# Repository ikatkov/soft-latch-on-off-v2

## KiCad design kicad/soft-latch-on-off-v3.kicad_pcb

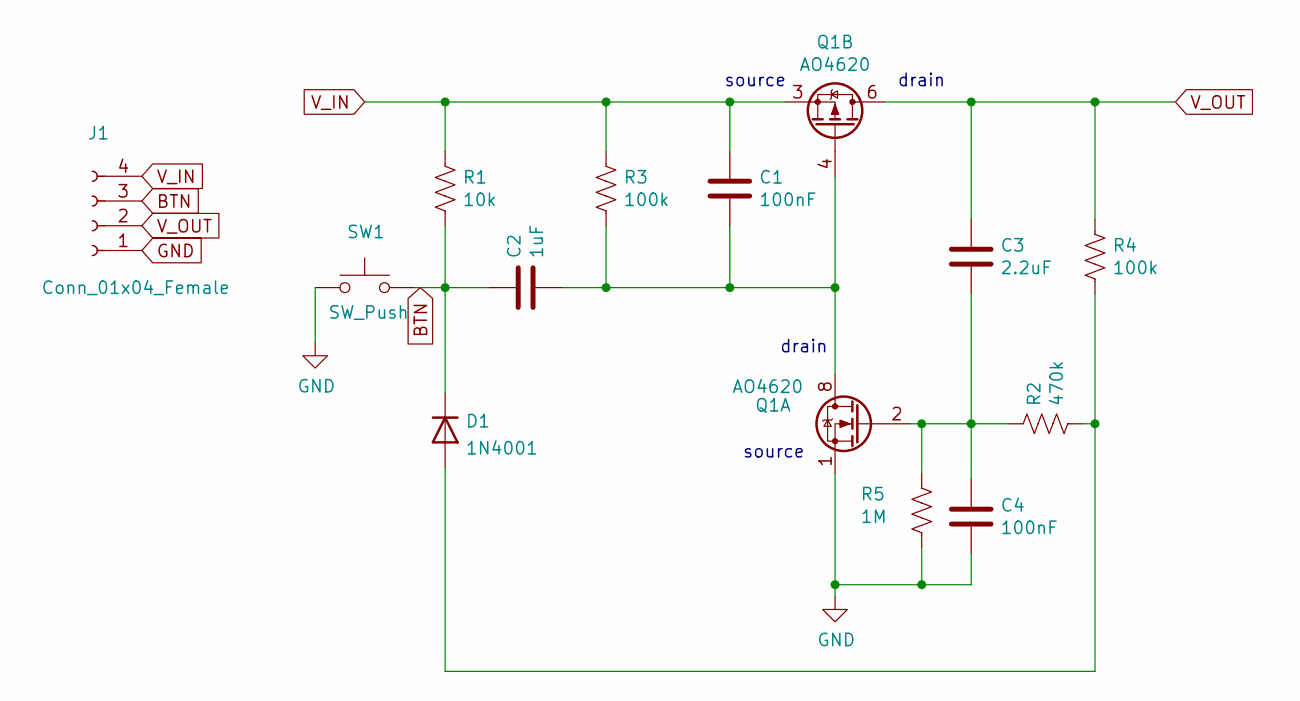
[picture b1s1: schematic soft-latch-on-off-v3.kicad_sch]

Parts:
C1, C4: 100nF; C_1206_3216Metric
C2: 1uF; C_1206_3216Metric
C3: 2.2uF; C_1206_3216Metric
D1: 1N4001; D_SMA
J1: Conn_01x04_Female; PinHeader_1x04_P2.54mm_Vertical
Q1: AO4620; SOIC-8_3.9x4.9mm_P1.27mm
R1: 10k; R_0805_2012Metric
R2: 470k; R_0805_2012Metric
R3, R4: 100k; R_0805_2012Metric
R5: 1M; R_0805_2012Metric
SW1: SW_Push; SW_PUSH_6mm

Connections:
BTN: C2.1, D1.1 (K), J1.3, R1.2, SW1.2
GND: C4.2, J1.1, Q1.1 (S), R5.2, SW1.1
unnamed: C1.2, C2.2, Q1.4 (G), Q1.7 (D), Q1.8 (D), R3.2
unnamed: C3.2, C4.1, Q1.2 (G), R2.1, R5.1
unnamed: D1.2 (A), R2.2, R4.2
V_IN: C1.1, J1.4, Q1.3 (1), R1.1, R3.1
V_OUT: C3.1, J1.2, Q1.5 (D), Q1.6 (D), R4.1

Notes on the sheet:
drain
source

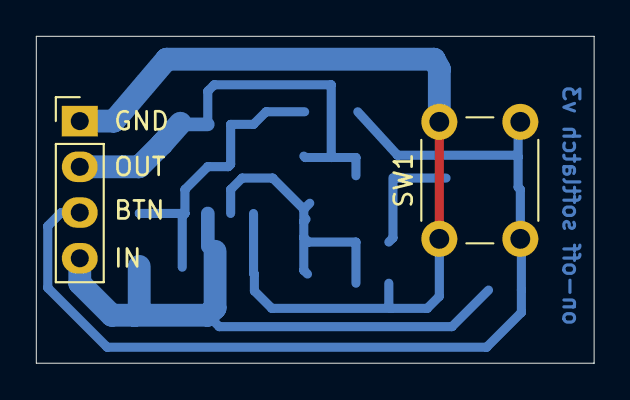
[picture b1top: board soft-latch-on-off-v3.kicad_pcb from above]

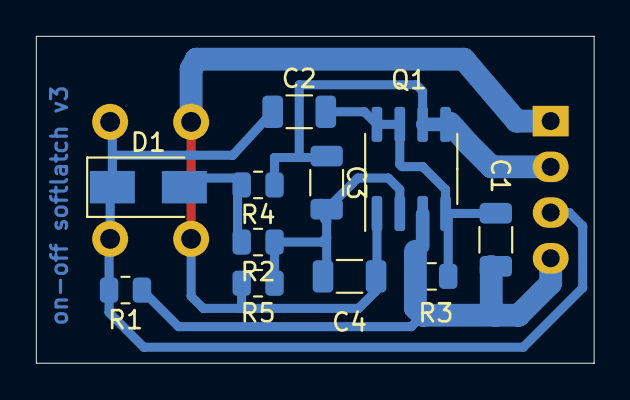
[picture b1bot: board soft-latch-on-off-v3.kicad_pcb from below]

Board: 2 copper layers, 31.0 x 18.2 mm, 13 parts (11 on the bottom side), 7 nets.
